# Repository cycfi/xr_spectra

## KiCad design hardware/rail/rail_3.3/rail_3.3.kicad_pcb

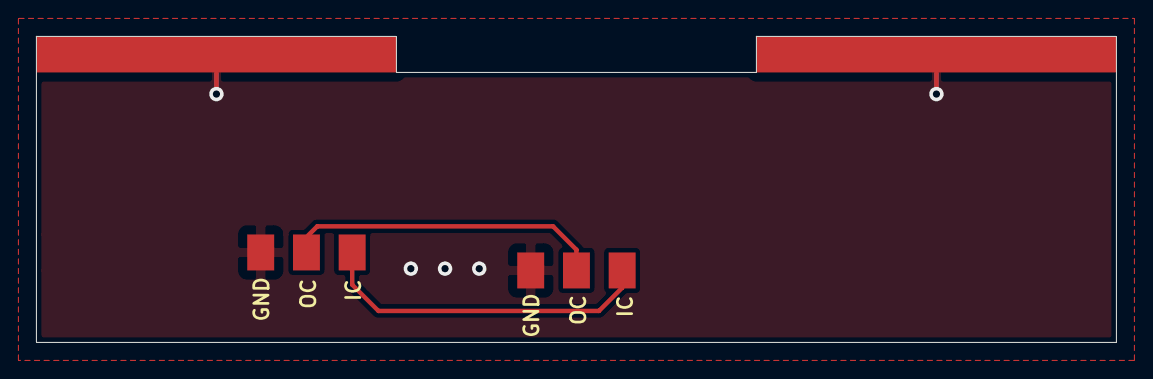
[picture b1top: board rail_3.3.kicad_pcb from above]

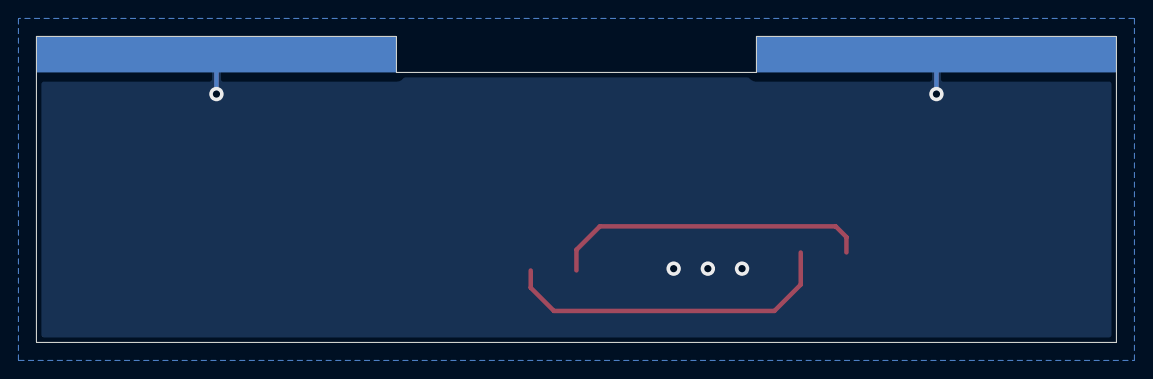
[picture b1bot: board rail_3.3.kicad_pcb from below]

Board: 2 copper layers, 60.0 x 17.0 mm, 6 parts (2 on the bottom side), 3 nets.

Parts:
H1, H2, H3, H4: single_pad_smd; single-pad-20x2
J1, J2: Conn_01x03; xr2-coil-connector-square

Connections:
/IC: J1.3, J2.3
/OC: J1.2, J2.2
GND: H1.1, H2.1, H3.1, H4.1, J1.1, J2.1

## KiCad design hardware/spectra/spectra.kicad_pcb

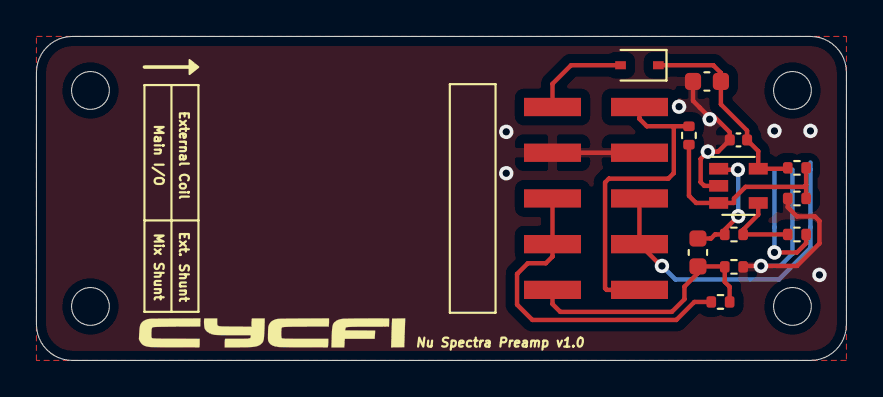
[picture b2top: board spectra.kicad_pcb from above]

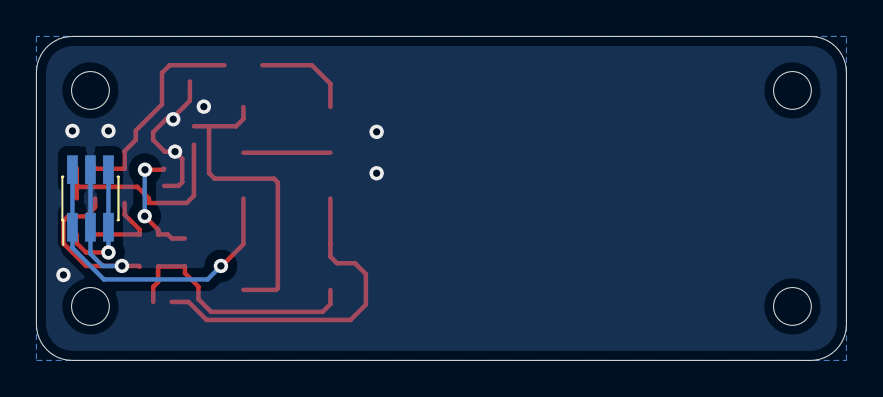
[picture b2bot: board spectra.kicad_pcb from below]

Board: 2 copper layers, 45.0 x 18.0 mm, 18 parts (5 on the bottom side), 11 nets.

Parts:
C1: 4.5uF; C_0603_1608Metric
C2: 0.1uF; C_0402_1005Metric
C3: 10uF; C_0603_1608Metric
D1: CUS551V30,H3F; D_SOD-323
H1, H2, H3, H4: MountingHole; mounting_hole_2.1mm
J1: I/O; pin_header_2x5p_2.54mm_smd_horizontal
J4: Coil; pin_socket_2x3p_1.00mm_smd_vertical
R1, R2: 39k; R_0402_1005Metric
R3, R4: 300k; R_0402_1005Metric
R5: 150k; R_0402_1005Metric
R6: 10k; R_0402_1005Metric
R7: 4.7k; R_0402_1005Metric
U1: TLV170DBV; SOT-23-5

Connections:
/IN-: J4.3, J4.4, R2.1
/VCC: D1.2, J1.6
GND: C1.2, C2.2, J1.4, J1.7, J4.2, J4.5, R4.2, R6.2, U1.2
unnamed: C3.2, R5.2, U1.1
unnamed: R1.1, R3.2, R4.1, U1.3
unnamed: R2.2, R5.1, U1.4
V+: C1.1, C2.1, D1.1, R3.1, U1.5
ext_coil+: J1.1, J1.5, R1.2
ext_coil-: J1.2, J1.3, J4.1, J4.6
mix: J1.8, J1.9, R7.1
out: C3.1, J1.10, R6.1, R7.2
